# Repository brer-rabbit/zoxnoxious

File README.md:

# Zoxnoxious Analog Synthesizer #

"Beyond Obnoxious"

Zoxnoxious is a hardware analog music synthesizer with a software interface.  The intent is to provide a platform for card/module development ("card" may be a better term than "module", as the latter is a well established term in the modular synth world).  Cards interface via a Raspberry Pi to a host controller over USB, and the host controller runs VCV Rack which provides control signals.

# Z-Cards #

Z-Cards are the voice cards that plug into the Zoxnoxious backplane.  Each card receives digital signals such as I2C and SPI along with analog signals from other Z-Cards.  Then each Z-Card drives a defined set of pins with its own analog output.

The Z-Cards are agnostic to the microcontroller; the interface being I2C and SPI most any microcontroller can be used.  While the overall Zoxnoxious project focuses on a Raspberry Pi implementation a different project can pickup the voice cards and do something different.  These cards are ripe for re-use in developing an analog synth with a microcontroller if you want to do your own thing and not use a Raspberry Pi like I have done in this project.

All Z-Cards are in the [kicad](kicad) directory.

Cards developed to date include:

* AS3340 VCO
* AS3372 Signal Processor (VCF, VCA)
* SSI2130/AS3394 Dual VCO + VCF Synth Voice
* Pole Dancer multimode filter with morphing/crossfade

The backplane design allows for up to 8 cards to be addressed with itself counting as one.  One control address goes unused as the backplane board design only has 6 physical slots.

# Raspberry Pi Host #

A Raspberry Pi Zero 2 attaches to the Zoxnoxious backplane.  To a host computer, the Pi appears as USB Audio and USB MIDI devices.  Incoming USB Audio and MIDI are dispatched to a card's driver, which may choose to send SPI or I2C messages to the card.

The application the Pi runs is contained entirely in the [raspberry_pi](raspberry_pi) directory.

# Zoxnoxious plugins for VCV Rack #

The user interacts with the synth through a VCV Rack plugin.  Zoxnoxious VCV Rack plugins map the Rack modules to audio channels and MIDI events that are sent via USB to the synthesizer.

These are all contained in the [vcv_rack](vcv_rack) directory.

# Deep Dive Videos

Deep dive 1: Project background and user interface

Deep dive 2: Raspberry Pi and Gadget mode

Deep dive 3: Hardware detail and autotune

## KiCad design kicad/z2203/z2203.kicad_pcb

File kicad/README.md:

# Zoxnoxious KiCad Files

The directories below contain KiCad files for the Zoxnoxious synthesizer.  This includes files for both schematics, PCB layout, and assembly.  Some boards also have a datasheet.

# Voice cards

* [Z2203](z2203/): Yamaha FM-based voice card with YM2203 chip
* [Pole Dancer](poledancer/): pole mixing filter utilizing an SSI2140 and SSI2190
* [Z3340](z3340/): Oscillator based around an AS3340 with four sync modes that can be combined
* [Z3372](z3372/): Lowpass filter with AS3372 filter chip.  Stereo panning, filter and resonance modulation.
* [Z5524](z5524/): dual VCO voice card.  SSI2130 oscillator for TZFM, AS3394 for second VCO and filter.  Powerful.

# Backplane

The [backplane](vca_backplane/) hosts six voice cards and a Raspberry Pi Zero2.

# Frontpanel

[Frontpanel](frontpanel/) for project.

# Template for development

The [zoxnoxiouscard](zoxnoxiouscard/) directory has a template to run from for creating voice cards.  Includes DAC, GPIO expander, and layout for the same.

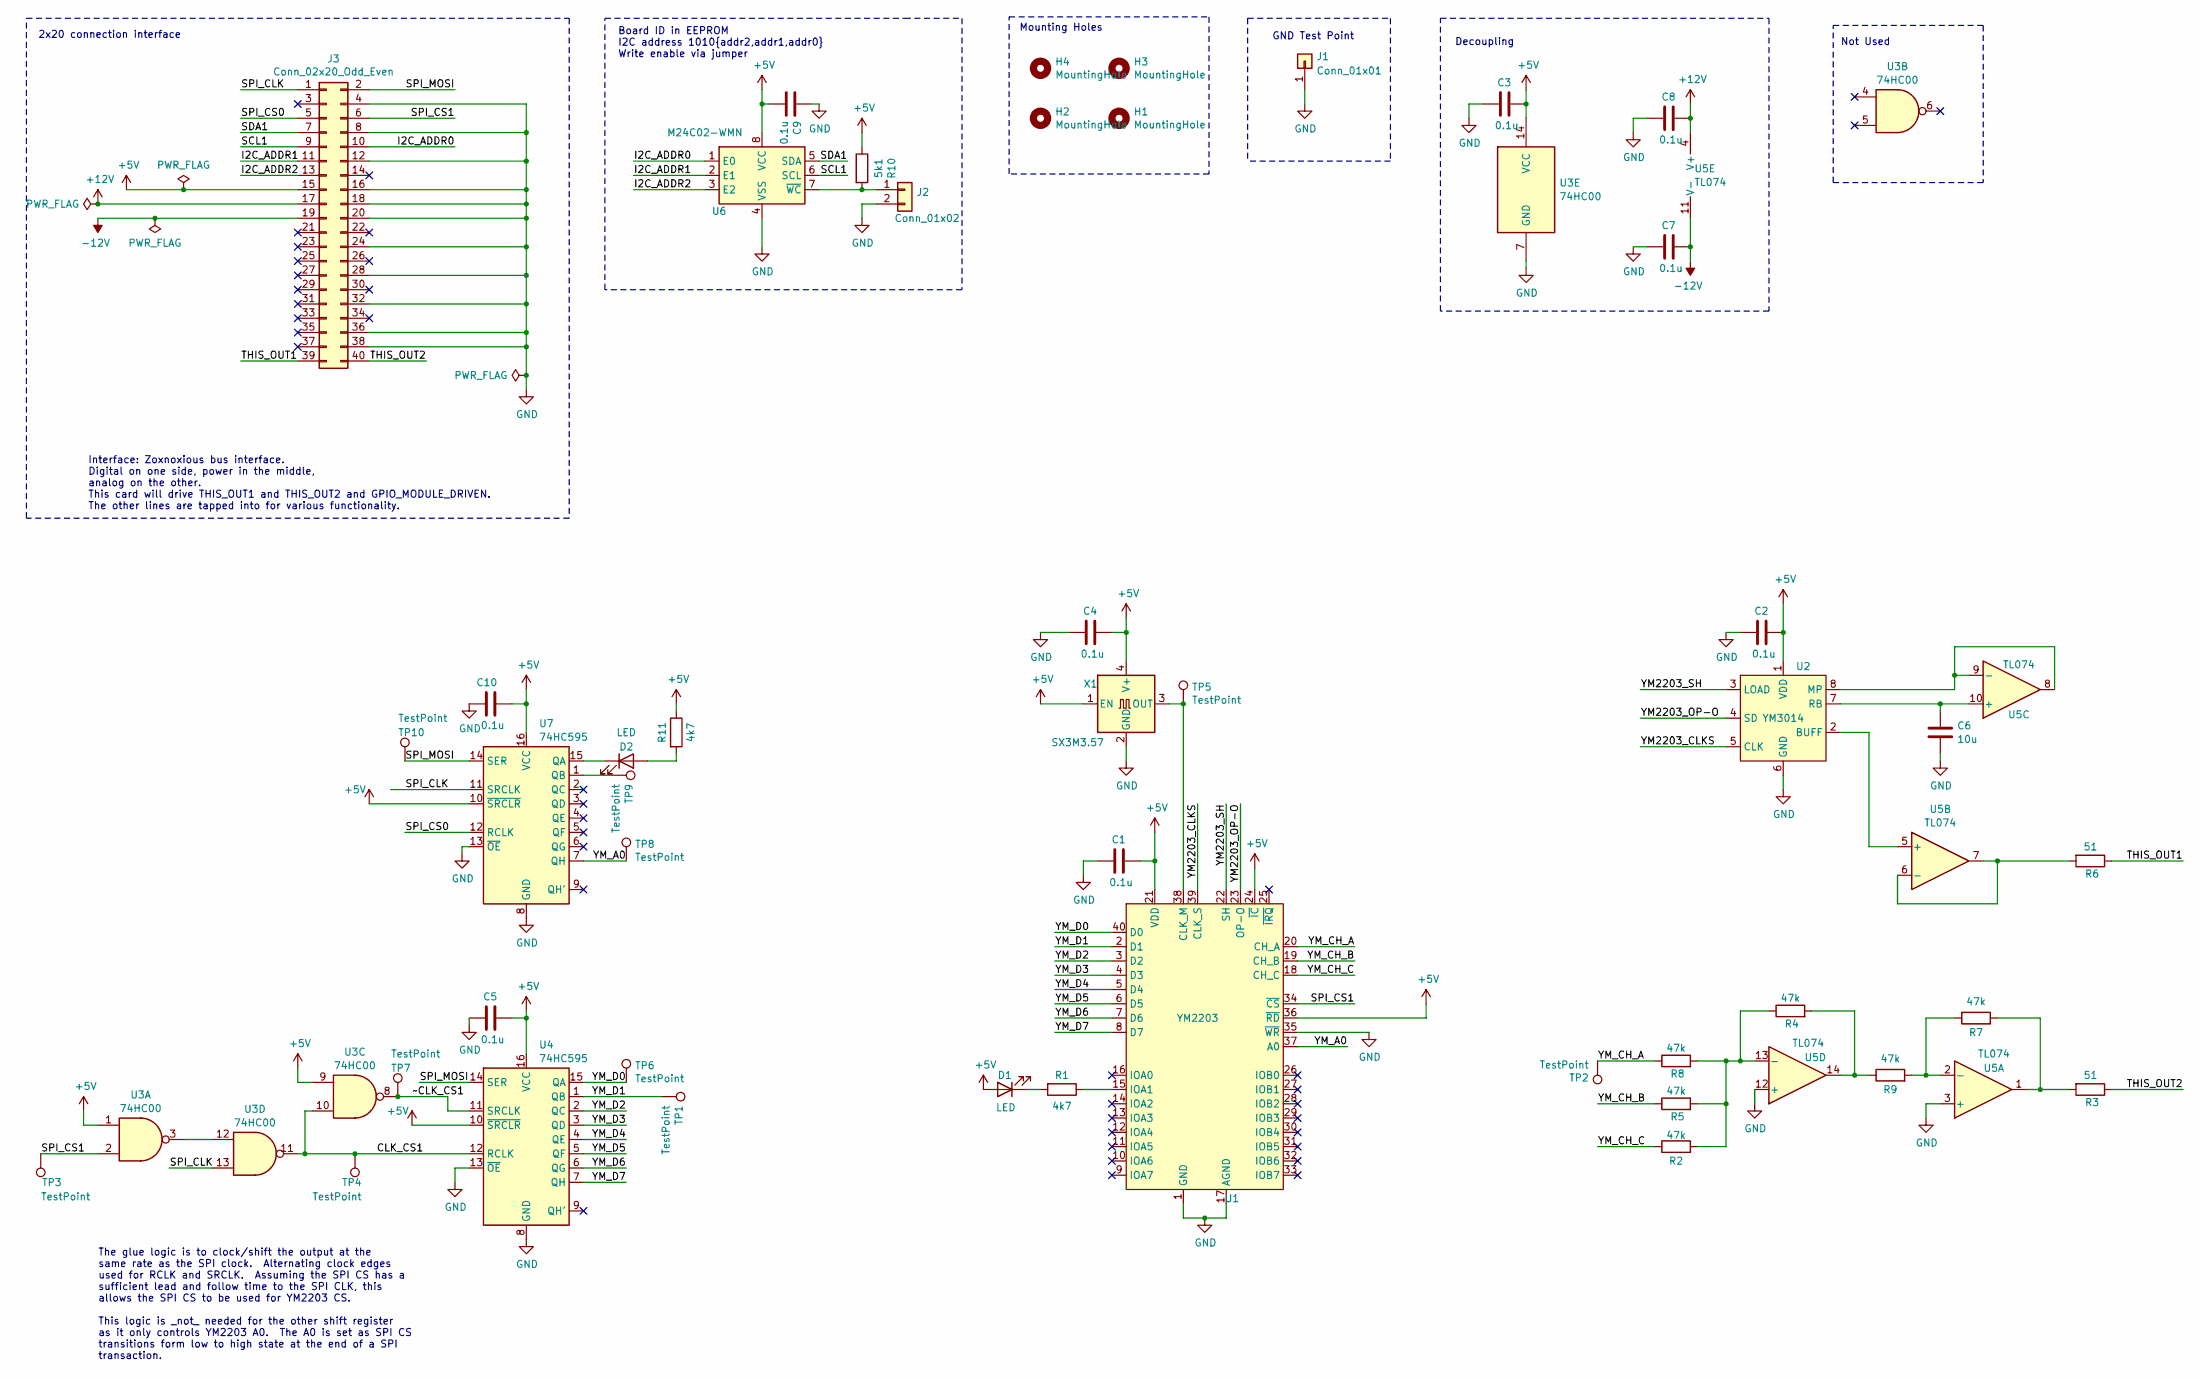
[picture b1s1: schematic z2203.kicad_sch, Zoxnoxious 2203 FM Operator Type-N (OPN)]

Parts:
C1, C2, C3, C4, C5, C7, C8, C9, C10: 0.1u; C_0603_1608Metric; LCSC C14663
C6: 10u; C_0805_2012Metric; LCSC C15850
D1, D2: LED; LED_0603_1608Metric; LCSC C2286
H1, H2, H3, H4: MountingHole; MountingHole_3.2mm_M3
J1: Conn_01x01; PinHeader_1x01_P2.54mm_Vertical
J2: Conn_01x02; PinHeader_1x02_P2.54mm_Vertical
J3: Conn_02x20_Odd_Even; PinHeader_2x20_P2.54mm_Horizontal
R1, R11: 4k7; R_0603_1608Metric; LCSC C23162
R2, R4, R5, R7, R8, R9: 47k; R_0603_1608Metric; LCSC C25819
R3, R6: 51; R_0603_1608Metric; LCSC C23197
R10: 5k1; R_0603_1608Metric; LCSC C23186
TP1, TP2, TP3, TP4, TP5, TP6, TP7, TP8, TP9, TP10: TestPoint; TestPoint_Pad_2.0x2.0mm; Digikey 952-2664-2-ND
U1: YM2203; DIP-40_W15.24mm
U2: YM3014; DIP-8_W7.62mm
U3: 74HC00; SOIC-14_3.9x8.7mm_P1.27mm; LCSC C10090
U4, U7: 74HC595; TSSOP-16_4.4x5mm_P0.65mm; LCSC C273642
U5: TL074; TSSOP-14_4.4x5mm_P0.65mm; LCSC C96507
U6: M24C02-WMN; SOIC-8_3.9x4.9mm_P1.27mm; LCSC C7562
X1: SX3M3.57; Oscillator_SMD_Abracon_ASE-4Pin_3.2x2.5mm; LCSC C41361373

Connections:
+5V: C1.2, C2.2, C3.2, C4.2, C5.2, C9.2, C10.2, D1.2 (A), J3.15, R10.1, R11.1, U1.21 (VDD), U1.24 (~IC), U1.36 (~RD), U2.1 (VDD), U3.1, U3.9, U3.14 (VCC), U4.10 (~SRCLR), U4.16 (VCC), U6.8 (VCC), U7.10 (~SRCLR), U7.16 (VCC), X1.1 (EN), X1.4 (V+)
+12V: C8.2, J3.17, U5.4 (V+)
-12V: C7.2, J3.19, U5.11 (V-)
/CLK_CS1: TP4.1, U3.10, U3.11, U4.12 (RCLK)
/I2C_ADDR0: J3.10, U6.1 (E0)
/I2C_ADDR1: J3.11, U6.2 (E1)
/I2C_ADDR2: J3.13, U6.3 (E2)
/SCL1: J3.9, U6.6 (SCL)
/SDA1: J3.7, U6.5 (SDA)
/SPI_CLK: J3.1, U3.13, U7.11 (SRCLK)
/SPI_CS0: J3.5, U7.12 (RCLK)
/SPI_CS1: J3.6, TP3.1, U1.34 (~CS), U3.2
/SPI_MOSI: J3.2, TP10.1, U4.14 (SER), U7.14 (SER)
/THIS_OUT1: J3.39, R6.1
/THIS_OUT2: J3.40, R3.1
/YM2203_CLKS: U1.39 (CLK_S), U2.5 (CLK)
/YM2203_OP-O: U1.23 (OP-O), U2.4 (SD)
/YM2203_SH: U1.22 (SH), U2.3 (LOAD)
/YM_A0: TP8.1, U1.37 (A0), U7.7 (QH)
/YM_CH_A: R8.1, TP2.1, U1.20 (CH_A)
/YM_CH_B: R5.1, U1.19 (CH_B)
/YM_CH_C: R2.1, U1.18 (CH_C)
/YM_D0: TP6.1, U1.40 (D0), U4.15 (QA)
/YM_D1: TP1.1, U1.2 (D1), U4.1 (QB)
/YM_D2: U1.3 (D2), U4.2 (QC)
/YM_D3: U1.4 (D3), U4.3 (QD)
/YM_D4: U1.5 (D4), U4.4 (QE)
/YM_D5: U1.6 (D5), U4.5 (QF)
/YM_D6: U1.7 (D6), U4.6 (QG)
/YM_D7: U1.8 (D7), U4.7 (QH)
/~CLK_CS1: TP7.1, U3.8, U4.11 (SRCLK)
GND: C1.1, C2.1, C3.1, C4.1, C5.1, C6.2, C7.1, C8.1, C9.1, C10.1, J1.1, J2.2, J3.4, J3.8, J3.12, J3.16, J3.18, J3.20, J3.24, J3.28, J3.32, J3.36, J3.38, U1.1 (GND), U1.17 (AGND), U1.35 (~WR), U2.6 (GND), U3.7 (GND), U4.8 (GND), U4.13 (~OE), U5.3 (+), U5.12 (+), U6.4 (VSS), U7.8 (GND), U7.13 (~OE), X1.2 (GND)
unnamed: D1.1 (K), R1.2
unnamed: D2.2 (A), R11.2
unnamed: D2.1 (K), U7.15 (QA)
unnamed: J2.1, R10.2, U6.7 (~WC)
unnamed: R3.2, R7.2, U5.1
unnamed: R4.2, R9.1, U5.14
unnamed: TP5.1, U1.38 (CLK_M), X1.3 (OUT)
unnamed: R1.1, U1.15 (IOA1)
unnamed: U2.2 (BUFF), U5.5 (+)
unnamed: U2.8 (MP), U5.8, U5.9 (-)
unnamed: C6.1, U2.7 (RB), U5.10 (+)
unnamed: U3.3, U3.12
unnamed: R7.1, R9.2, U5.2 (-)
unnamed: R6.2, U5.6 (-), U5.7
unnamed: R2.2, R4.1, R5.2, R8.2, U5.13 (-)
unnamed: TP9.1, U7.1 (QB)

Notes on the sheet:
The glue logic is to clock/shift the output at the same rate as the SPI clock. Alternating clock edges used for RCLK and SRCLK. Assuming the SPI CS has a sufficient lead and follow time to the SPI CLK, this allows the SPI CS to be used for YM2203 CS. This logic is _not_ needed for the other shift r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
2x20 connection interface
Decoupling
Mounting Holes
GND Test Point
Board ID in EEPROM I2C address 1010{addr2,addr1,addr0} Write enable via jumper
Not Used
Interface: Zoxnoxious bus interface. Digital on one side, power in the middle, analog on the other. This card will drive THIS_OUT1 and THIS_OUT2 and GPIO_MODULE_DRIVEN. The other lines are tapped into for various functionality.

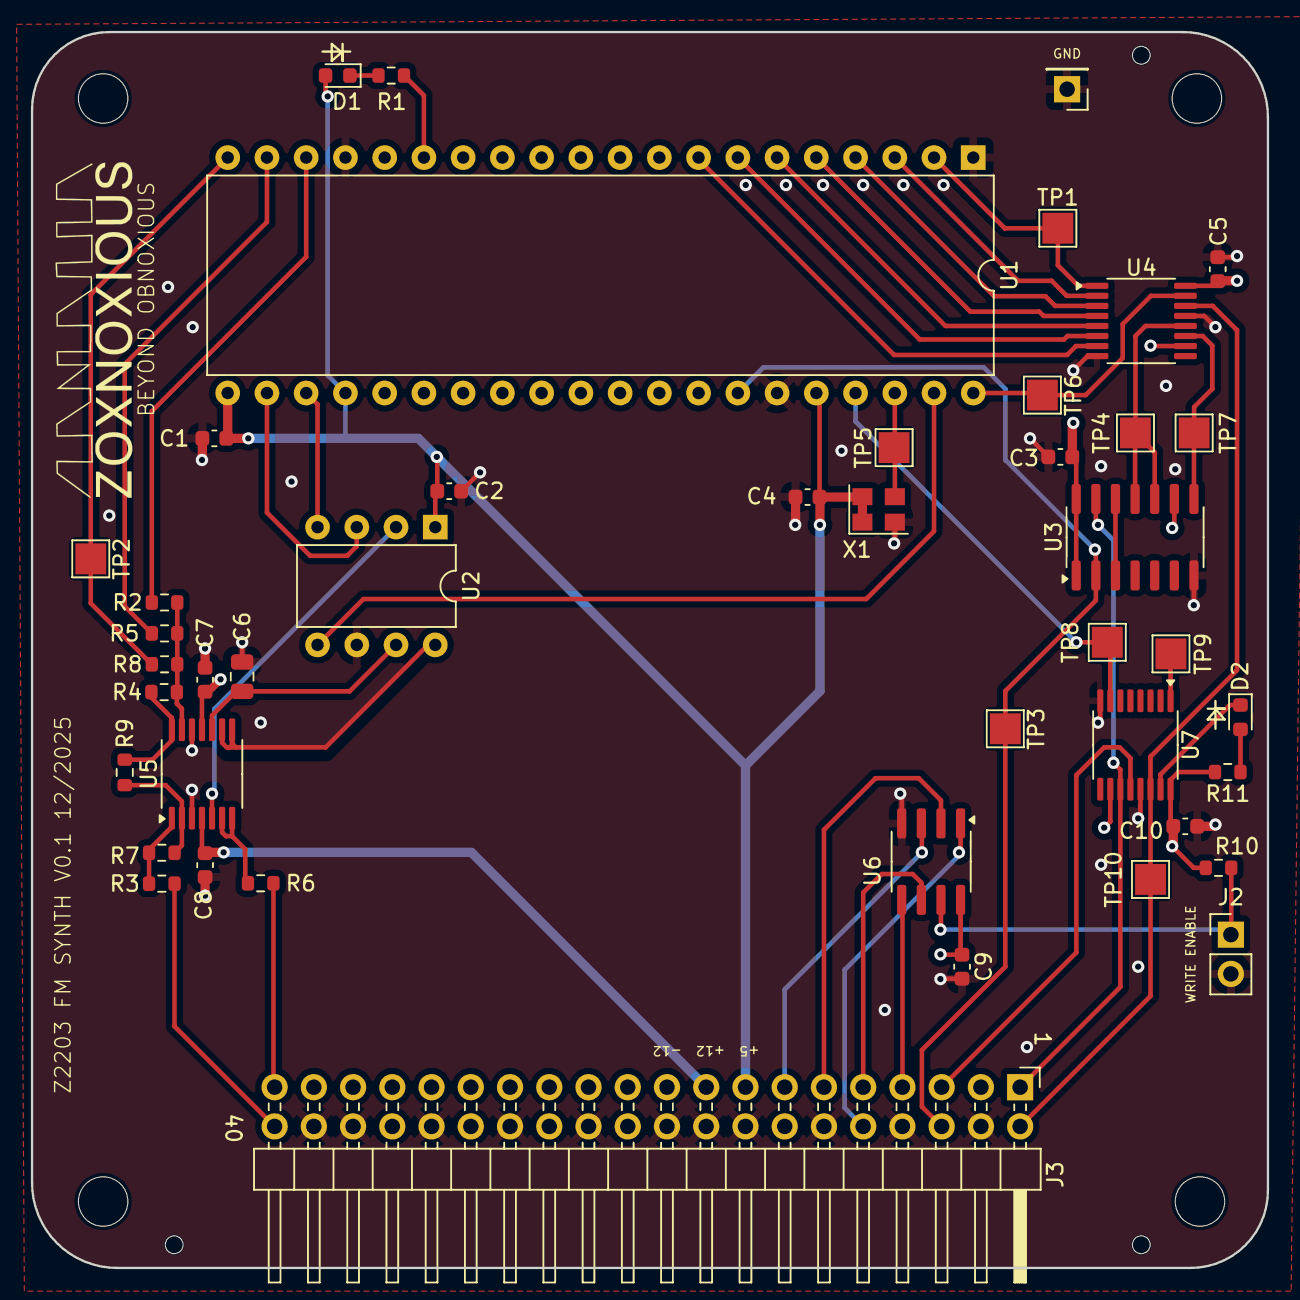
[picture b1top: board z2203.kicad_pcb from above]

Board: 4 copper layers, 80.0 x 80.0 mm, 48 parts (0 on the bottom side), 48 nets.

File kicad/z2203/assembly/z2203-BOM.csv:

Comment,Designator,Footprint,LCSC
"0.1u","C1,C2,C3,C4,C5,C7,C8,C9,C10","Capacitor_SMD:C_0603_1608Metric","C14663"
"10u","C6","Capacitor_SMD:C_0805_2012Metric","C15850"
"LED","D1,D2","LED_SMD:LED_0603_1608Metric","C2286"
"Conn_01x01","J1","Connector_PinHeader_2.54mm:PinHeader_1x01_P2.54mm_Vertical",""
"Conn_01x02","J2","Connector_PinHeader_2.54mm:PinHeader_1x02_P2.54mm_Vertical",""
"Conn_02x20_Odd_Even","J3","Connector_PinHeader_2.54mm:PinHeader_2x20_P2.54mm_Horizontal",""
"4k7","R1,R11","Resistor_SMD:R_0603_1608Metric","C23162"
"5k1","R10","Resistor_SMD:R_0603_1608Metric","C23186"
"47k","R2,R4,R5,R7,R8,R9","Resistor_SMD:R_0603_1608Metric","C25819"
"51","R3,R6","Resistor_SMD:R_0603_1608Metric","C23197"
"TestPoint","TP1,TP2,TP3,TP4,TP5,TP6,TP7,TP8,TP9,TP10","TestPoint:TestPoint_Pad_2.0x2.0mm",""
"YM2203","U1","Package_DIP:DIP-40_W15.24mm",""
"YM3014","U2","Package_DIP:DIP-8_W7.62mm",""
"74HC00","U3","Package_SO:SOIC-14_3.9x8.7mm_P1.27mm","C10090"
"74HC595","U4,U7","Package_SO:TSSOP-16_4.4x5mm_P0.65mm","C273642"
"TL074","U5","Package_SO:TSSOP-14_4.4x5mm_P0.65mm","C96507"
"M24C02-WMN","U6","Package_SO:SOIC-8_3.9x4.9mm_P1.27mm","C7562"
"SX3M3.57","X1","Oscillator:Oscillator_SMD_Abracon_ASE-4Pin_3.2x2.5mm","C41361373"

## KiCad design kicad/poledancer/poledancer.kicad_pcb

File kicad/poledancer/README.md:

# Pole Dancer Multimode Pole Mixing Filter

The Pole Dancer may be the most versatile analog synthesizer filter.  Built around an SSI2140 four pole filter and an SSI2190 mixer provides the pole mixing.  A number of filter modes are possible using the filter mixing.  The real fun is morphing between filter modes, which can be done with manipulating the '2190 mixer.

Multiple resonance compensation modes, in addition to uncompensated, give a wide range of character.

# Block Diagram

# Resources

Datasheet TBD

[KiCanvas](https://kicanvas.org/?github=https%3A%2F%2Fgithub.com%2Fbrer-rabbit%2Fzoxnoxious%2Ftree%2Fmain%2Fkicad%2Fpoledancer)

# Demo

YouTube Demo

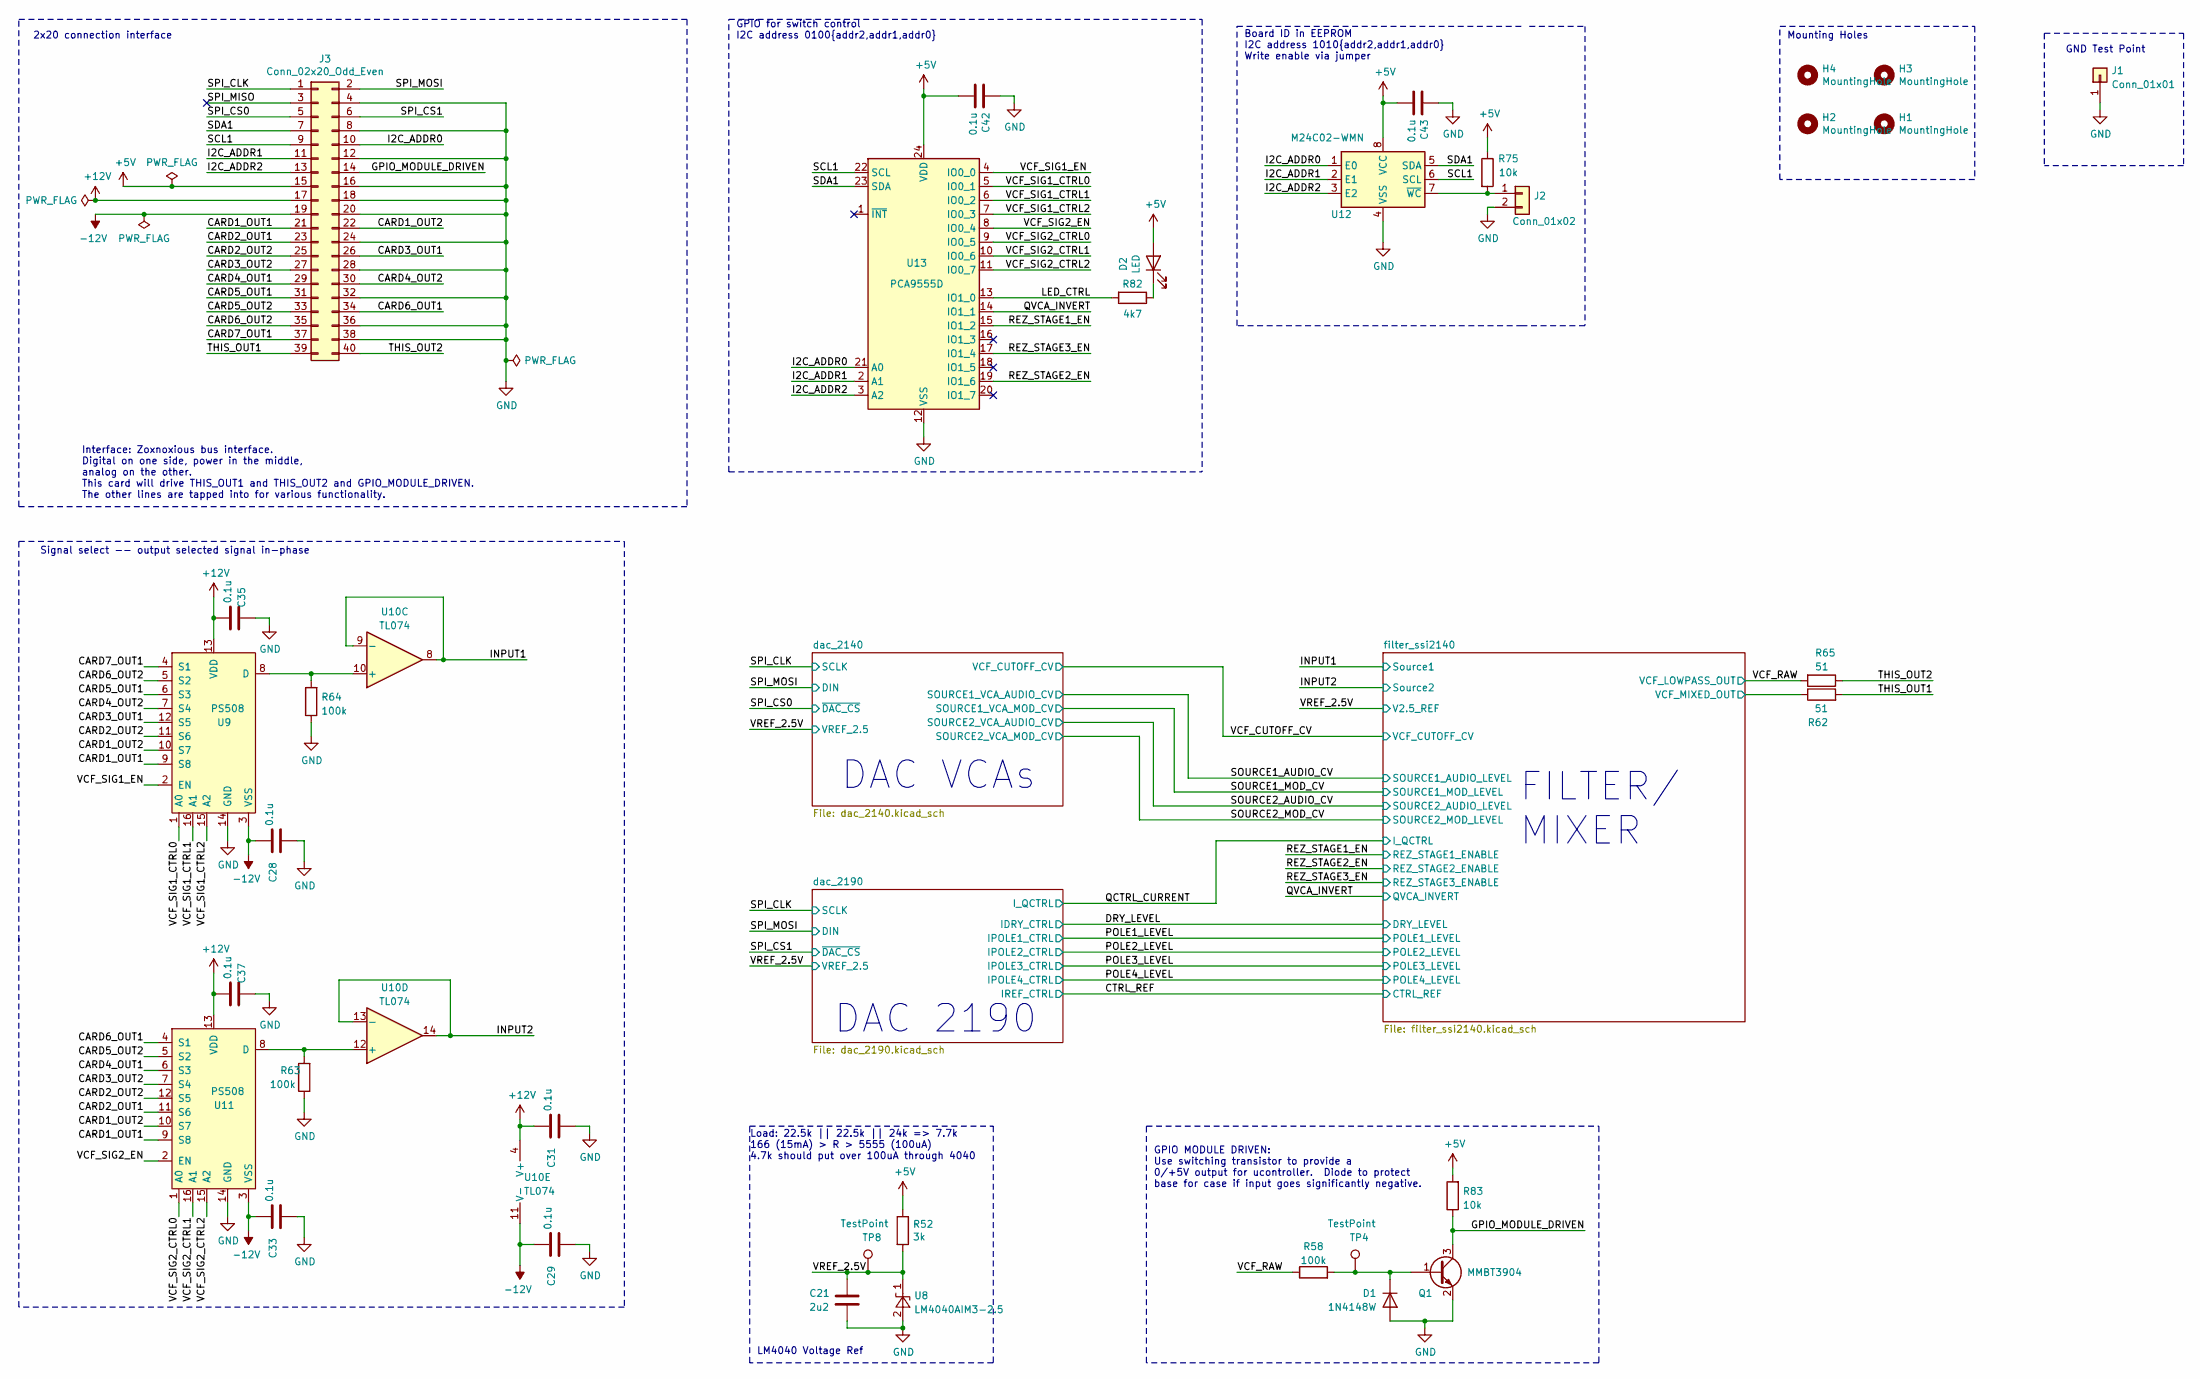
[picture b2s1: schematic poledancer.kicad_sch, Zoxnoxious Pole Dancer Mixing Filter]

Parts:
C21: 2u2; C_0603_1608Metric; LCSC C23630
C28, C29, C31, C33, C35, C37, C42, C43: 0.1u; C_0603_1608Metric; LCSC C14663
D1: 1N4148W; D_SOD-123; LCSC C81598
D2: LED; LED_0603_1608Metric; LCSC C2286
H1, H2, H3, H4: MountingHole; MountingHole_3.2mm_M3
J1: Conn_01x01; PinHeader_1x01_P2.54mm_Vertical
J2: Conn_01x02; PinHeader_1x02_P2.54mm_Vertical
J3: Conn_02x20_Odd_Even; PinHeader_2x20_P2.54mm_Horizontal
Q1: MMBT3904; SOT-23; LCSC C20526
R52: 3k; R_0603_1608Metric; LCSC C4211
R58, R63, R64: 100k; R_0603_1608Metric; LCSC C25803
R62, R65: 51; R_0603_1608Metric; LCSC C23197
R75, R83: 10k; R_0603_1608Metric; LCSC C25804
R82: 4k7; R_0603_1608Metric; LCSC C23162
TP4, TP8: TestPoint; TestPoint_Pad_2.0x2.0mm
U8: LM4040AIM3-2.5; SOT-23; LCSC C111866
U9, U11: PS508; SOIC-16_3.9x9.9mm_P1.27mm; LCSC C2673104
U10: TL074; TSSOP-14_4.4x5mm_P0.65mm; LCSC C96507
U12: M24C02-WMN; SOIC-8_3.9x4.9mm_P1.27mm; LCSC C7562
U13: PCA9555D; TSSOP-24_4.4x7.8mm_P0.65mm; LCSC C83265

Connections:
+5V: C42.2, C43.2, D2.2 (A), J3.15, R52.1, R75.1, R83.2, U12.8 (VCC), U13.24 (VDD); also elsewhere on the board
+12V: C31.2, C35.2, C37.2, J3.17, U9.13 (VDD), U10.4 (V+), U11.13 (VDD); also elsewhere on the board
-12V: C28.2, C29.2, C33.2, J3.19, U9.3 (VSS), U10.11 (V-), U11.3 (VSS); also elsewhere on the board
/CARD1_OUT1: J3.21, U9.9 (S8), U11.9 (S8)
/CARD1_OUT2: J3.22, U9.10 (S7), U11.10 (S7)
/CARD2_OUT1: J3.23, U11.11 (S6)
/CARD2_OUT2: J3.25, U9.11 (S6), U11.12 (S5)
/CARD3_OUT1: J3.26, U9.12 (S5)
/CARD3_OUT2: J3.27, U11.7 (S4)
/CARD4_OUT1: J3.29, U11.6 (S3)
/CARD4_OUT2: J3.30, U9.7 (S4)
/CARD5_OUT1: J3.31, U9.6 (S3)
/CARD5_OUT2: J3.33, U11.5 (S2)
/CARD6_OUT1: J3.34, U11.4 (S1)
/CARD6_OUT2: J3.35, U9.5 (S2)
/CARD7_OUT1: J3.37, U9.4 (S1)
/GPIO_MODULE_DRIVEN: J3.14, Q1.3 (C), R83.1
/I2C_ADDR0: J3.10, U12.1 (E0), U13.21 (A0)
/I2C_ADDR1: J3.11, U12.2 (E1), U13.2 (A1)
/I2C_ADDR2: J3.13, U12.3 (E2), U13.3 (A2)
/INPUT1: U10.8, U10.9 (-); also elsewhere on the board
/INPUT2: U10.13 (-), U10.14; also elsewhere on the board
/LED_CTRL: R82.2, U13.13 (IO1_0)
/QVCA_INVERT: U13.14 (IO1_1); also elsewhere on the board
/REZ_STAGE1_EN: U13.15 (IO1_2); also elsewhere on the board
/REZ_STAGE2_EN: U13.19 (IO1_6); also elsewhere on the board
/REZ_STAGE3_EN: U13.17 (IO1_4); also elsewhere on the board
/SCL1: J3.9, U12.6 (SCL), U13.22 (SCL)
/SDA1: J3.7, U12.5 (SDA), U13.23 (SDA)
/SPI_CLK: J3.1; also elsewhere on the board
/SPI_CS0: J3.5; also elsewhere on the board
/SPI_CS1: J3.6; also elsewhere on the board
/SPI_MISO: J3.3
/SPI_MOSI: J3.2; also elsewhere on the board
/THIS_OUT1: J3.39, R62.2
/THIS_OUT2: J3.40, R65.1
/VCF_RAW: R58.1, R65.2; also elsewhere on the board
/VCF_SIG1_CTRL0: U9.1 (A0), U13.5 (IO0_1)
/VCF_SIG1_CTRL1: U9.16 (A1), U13.6 (IO0_2)
/VCF_SIG1_CTRL2: U9.15 (A2), U13.7 (IO0_3)
/VCF_SIG1_EN: U9.2 (EN), U13.4 (IO0_0)
/VCF_SIG2_CTRL0: U11.1 (A0), U13.9 (IO0_5)
/VCF_SIG2_CTRL1: U11.16 (A1), U13.10 (IO0_6)
/VCF_SIG2_CTRL2: U11.15 (A2), U13.11 (IO0_7)
/VCF_SIG2_EN: U11.2 (EN), U13.8 (IO0_4)
/VREF_2.5V: C21.1, R52.2, TP8.1, U8.1 (K); also elsewhere on the board
/filter_ssi2140/VCF_MIXED_OUT: R62.1; also elsewhere on the board
GND: C21.2, C28.1, C29.1, C31.1, C33.1, C35.1, C37.1, C42.1, C43.1, D1.2 (A), J1.1, J2.2, J3.4, J3.8, J3.12, J3.16, J3.18, J3.20, J3.24, J3.28, J3.32, J3.36, J3.38, Q1.2 (E), R63.1, R64.1, U8.2 (A), U9.14 (GND), U11.14 (GND), U12.4 (VSS), U13.12 (VSS); also elsewhere on the board
unnamed: D1.1 (K), Q1.1 (B), R58.2, TP4.1
unnamed: D2.1 (K), R82.1
unnamed: J2.1, R75.2, U12.7 (~WC)
unnamed: R64.2, U9.8 (D), U10.10 (+)
unnamed: R63.2, U10.12 (+), U11.8 (D)

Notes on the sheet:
Load: 22.5k || 22.5k || 24k => 7.7k 166 (15mA) > R > 5555 (100uA) 4.7k should put over 100uA through 4040
Signal select -- output selected signal in-phase
GPIO MODULE DRIVEN: Use switching transistor to provide a 0/+5V output for ucontroller. Diode to protect base for case if input goes significantly negative.
2x20 connection interface
FILTER/ MIXER
GPIO for switch control I2C address 0100{addr2,addr1,addr0}
Mounting Holes
DAC 2190
GND Test Point
Board ID in EEPROM I2C address 1010{addr2,addr1,addr0} Write enable via jumper
Interface: Zoxnoxious bus interface. Digital on one side, power in the middle, analog on the other. This card will drive THIS_OUT1 and THIS_OUT2 and GPIO_MODULE_DRIVEN. The other lines are tapped into for various functionality.
LM4040 Voltage Ref
DAC VCAs

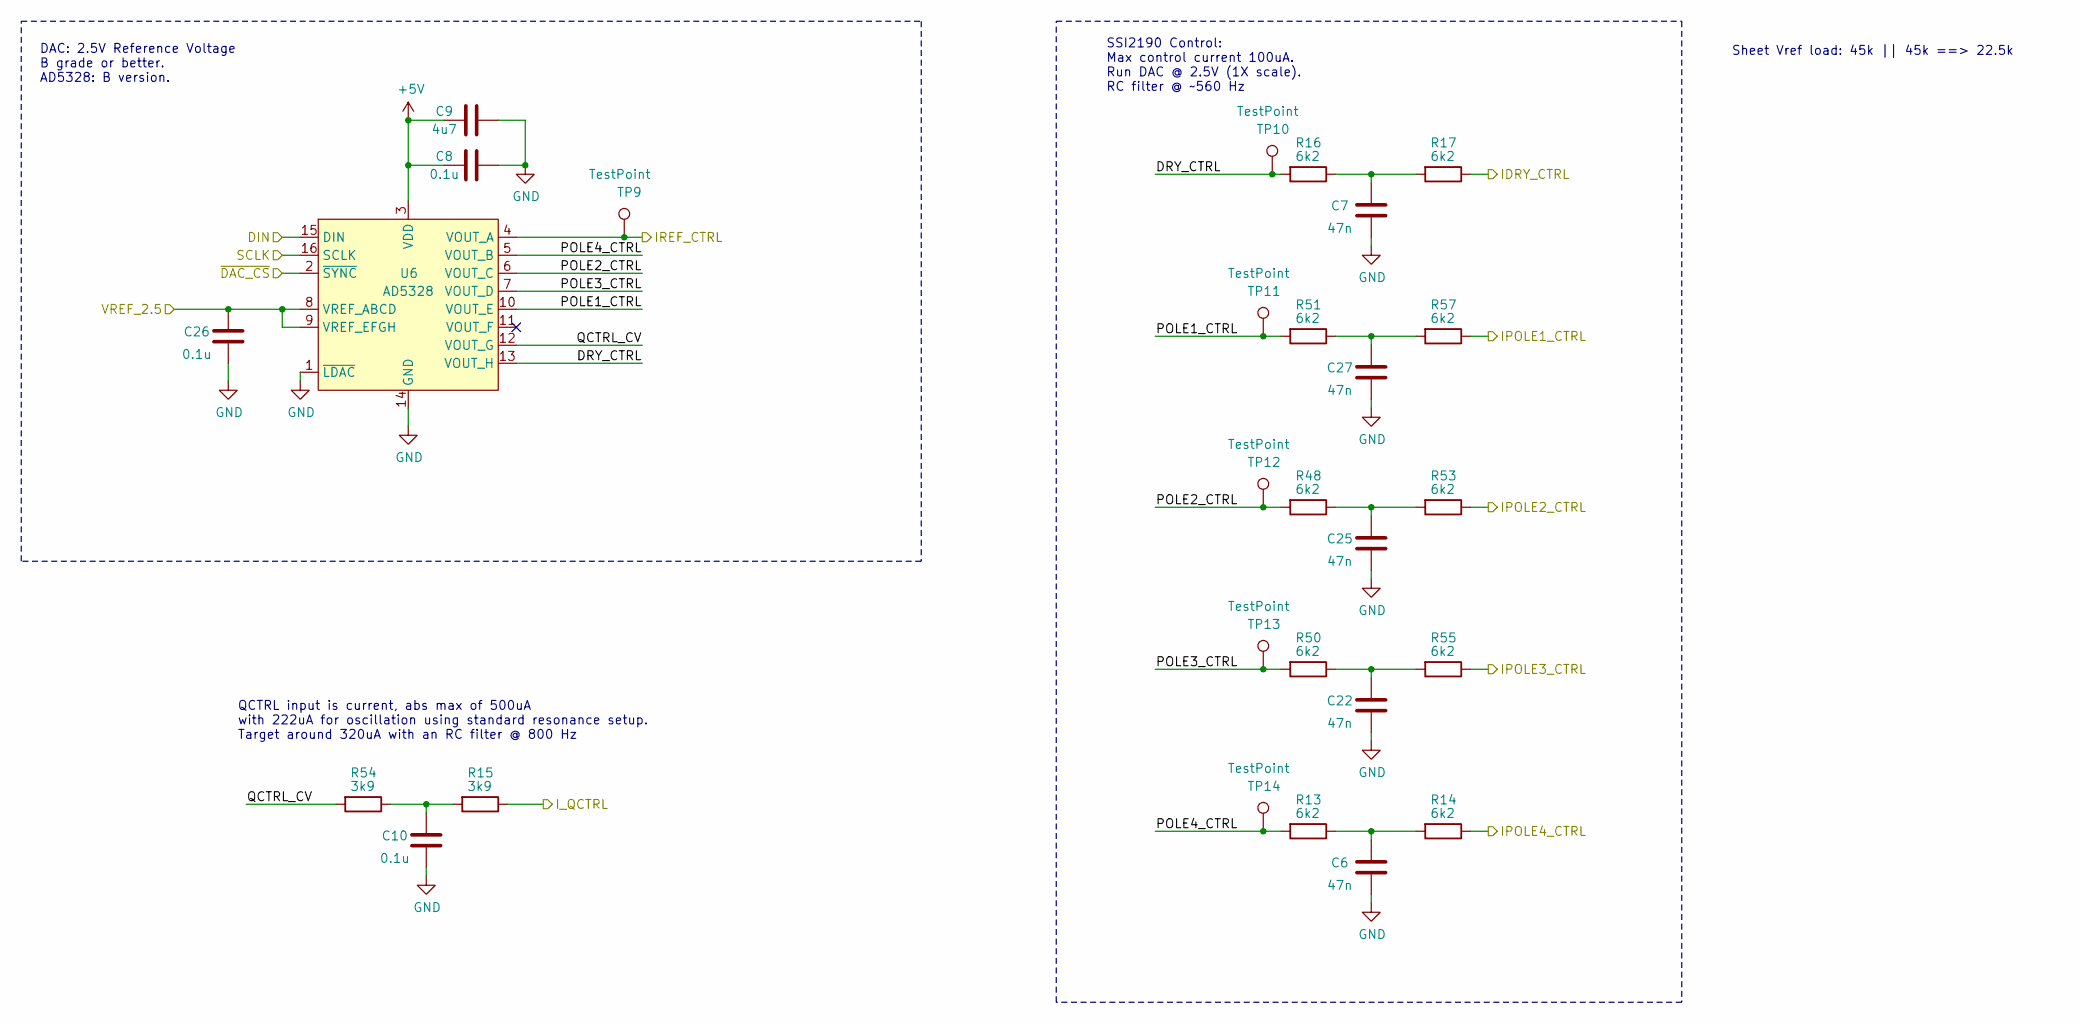
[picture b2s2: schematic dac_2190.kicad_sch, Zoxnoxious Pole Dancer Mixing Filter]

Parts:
C6, C7, C22, C25, C27: 47n; C_0603_1608Metric; LCSC C1622
C8, C10, C26: 0.1u; C_0603_1608Metric; LCSC C14663
C9: 4u7; C_0603_1608Metric; LCSC C19666
R13, R14, R16, R17, R48, R50, R51, R53, R55, R57: 6k2; R_0603_1608Metric; LCSC C4260
R15, R54: 3k9; R_0603_1608Metric; LCSC C23018
TP9, TP10, TP11, TP12, TP13, TP14: TestPoint; TestPoint_Pad_2.0x2.0mm
U6: AD5328; TSSOP-16_4.4x5mm_P0.65mm; LCSC C29162

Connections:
+5V: C8.1, C9.1, U6.3 (VDD); also elsewhere on the board
/CTRL_REF: TP9.1, U6.4 (VOUT_A); also elsewhere on the board
/DRY_LEVEL: R17.1; also elsewhere on the board
/POLE1_LEVEL: R57.1; also elsewhere on the board
/POLE2_LEVEL: R53.1; also elsewhere on the board
/POLE3_LEVEL: R55.1; also elsewhere on the board
/POLE4_LEVEL: R14.1; also elsewhere on the board
/QCTRL_CURRENT: R15.1; also elsewhere on the board
/SPI_CLK: U6.16 (SCLK); also elsewhere on the board
/SPI_CS1: U6.2 (~SYNC); also elsewhere on the board
/SPI_MOSI: U6.15 (DIN); also elsewhere on the board
/VREF_2.5V: C26.1, U6.8 (VREF_ABCD), U6.9 (VREF_EFGH); also elsewhere on the board
/dac_2190/DRY_CTRL: R16.2, TP10.1, U6.13 (VOUT_H)
/dac_2190/POLE1_CTRL: R51.2, TP11.1, U6.10 (VOUT_E)
/dac_2190/POLE2_CTRL: R48.2, TP12.1, U6.6 (VOUT_C)
/dac_2190/POLE3_CTRL: R50.2, TP13.1, U6.7 (VOUT_D)
/dac_2190/POLE4_CTRL: R13.2, TP14.1, U6.5 (VOUT_B)
/dac_2190/QCTRL_CV: R54.2, U6.12 (VOUT_G)
GND: C6.2, C7.2, C8.2, C9.2, C10.2, C22.2, C25.2, C26.2, C27.2, U6.1 (~LDAC), U6.14 (GND); also elsewhere on the board
unnamed: C6.1, R13.1, R14.2
unnamed: C7.1, R16.1, R17.2
unnamed: C10.1, R15.2, R54.1
unnamed: C22.1, R50.1, R55.2
unnamed: C25.1, R48.1, R53.2
unnamed: C27.1, R51.1, R57.2

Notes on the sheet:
QCTRL input is current, abs max of 500uA with 222uA for oscillation using standard resonance setup. Target around 320uA with an RC filter @ 800 Hz
SSI2190 Control: Max control current 100uA. Run DAC @ 2.5V (1X scale). RC filter @ ~560 Hz
Sheet Vref load: 45k || 45k ==> 22.5k
DAC: 2.5V Reference Voltage B grade or better. AD5328: B version.
